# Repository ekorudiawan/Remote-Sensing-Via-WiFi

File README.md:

# Remote-Sensing-Via-WiFi
Remote Sensing Via WiFi

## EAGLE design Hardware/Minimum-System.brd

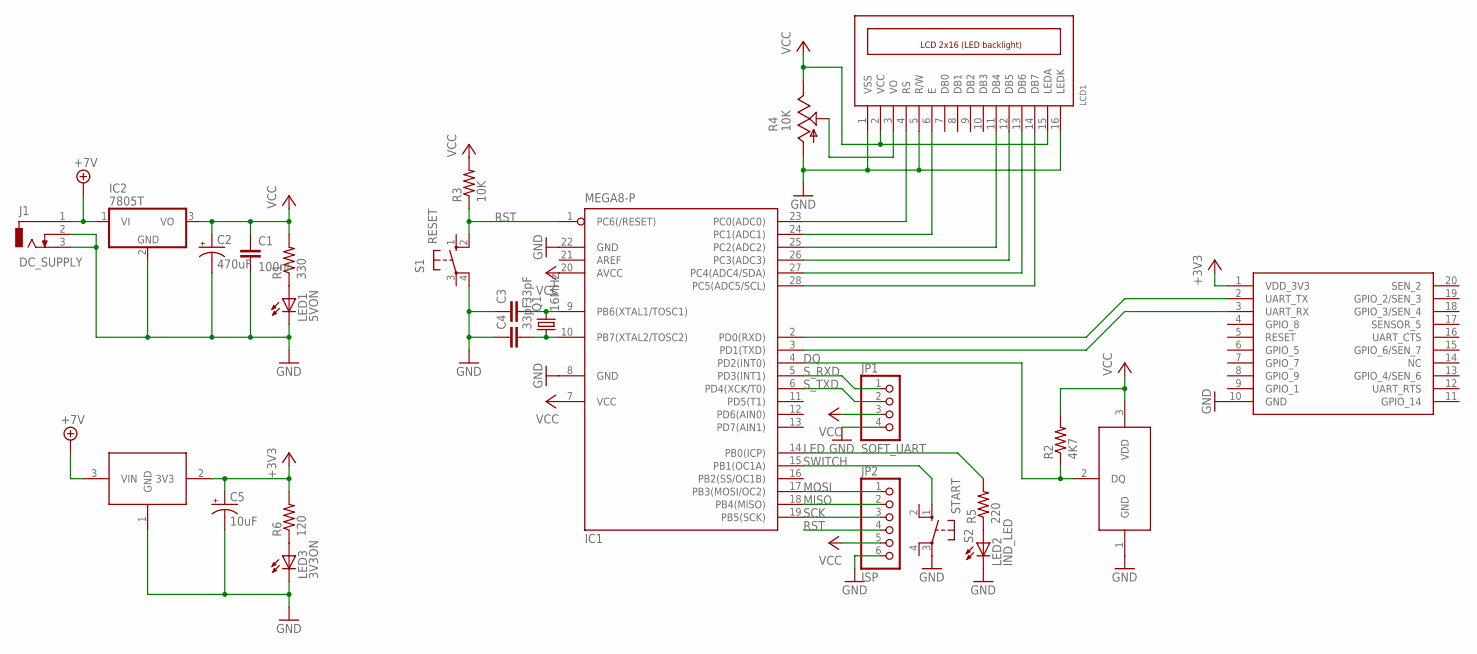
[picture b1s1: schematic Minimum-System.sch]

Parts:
C1: 100nF; C025-024X044
C2: 470uF; E2,5-7
C3, C4: 33pF; C025-024X044
C5: 10uF; E2,5-7
IC1: MEGA8-P; DIL28-3
IC2: 7805T; TO220H
J1: DC_SUPPLY; DCJ0202
JP1: SOFT_UART; 1X04
JP2: ISP; 1X06
LCD1: LCD_2X16; HY-1602F
LED1: 5VON; LED3MM
LED2: IND_LED; LED3MM
LED3: 3V3ON; LED3MM
Q1: 16MHz; HC49/S
R1: 330; 0207/10
R2: 4K7; 0207/10
R3: 10K; 0207/10
R4: 10K; CA6V
R5: 220; 0207/10
R6: 120; 0207/10
S1: RESET; B3F-10XX
S2: START; B3F-10XX
U1: DS1820; TO92
U2: LD1117V33; TO220
U3: WIFLY; WIFLY_SOCKET

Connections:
+3V3: C5.+, R6.2, U2.2 (3V3), U3.1 (VDD_3V3)
+7V: IC2.1 (VI), J1.1, U2.3 (VIN)
DQ: IC1.4 (PD2(INT0)), R2.1, U1.2 (DQ)
GND: C1.2, C2.-, C3.1, C4.1, C5.-, IC1.8 (GND), IC1.22 (GND), IC2.2 (GND), J1.2, J1.3, JP1.4, JP2.6, LCD1.1 (VSS), LCD1.5 (R/W), LCD1.16 (LEDK), LED1.K (C), LED2.K (C), LED3.K (C), R4.A, S1.4 (P1), S2.3, U1.1 (GND), U2.1 (GND), U3.10 (GND)
LED: IC1.14 (PB0(ICP)), R5.2
MISO: IC1.18 (PB4(MISO)), JP2.2
MOSI: IC1.17 (PB3(MOSI/OC2)), JP2.1
unnamed: LED1.A, R1.1
unnamed: IC1.25 (PC2(ADC2)), LCD1.11 (DB4)
unnamed: LCD1.3 (VO), R4.S
unnamed: IC1.23 (PC0(ADC0)), LCD1.4 (RS)
unnamed: C3.2, IC1.9 (PB6(XTAL1/TOSC1)), Q1.2
unnamed: C4.2, IC1.10 (PB7(XTAL2/TOSC2)), Q1.1
unnamed: IC1.24 (PC1(ADC1)), LCD1.6 (E)
unnamed: IC1.26 (PC3(ADC3)), LCD1.12 (DB5)
unnamed: IC1.27 (PC4(ADC4/SDA)), LCD1.13 (DB6)
unnamed: IC1.28 (PC5(ADC5/SCL)), LCD1.14 (DB7)
unnamed: IC1.2 (PD0(RXD)), U3.2 (UART_TX)
unnamed: IC1.3 (PD1(TXD)), U3.3 (UART_RX)
unnamed: LED2.A, R5.1
unnamed: LED3.A, R6.1
RST: IC1.1 (PC6(/RESET)), JP2.4, R3.1, S1.2 (S1)
SCK: IC1.19 (PB5(SCK)), JP2.3
SWITCH: IC1.15 (PB1(OC1A)), S2.1 (S)
S_RXD: IC1.5 (PD3(INT1)), JP1.1
S_TXD: IC1.6 (PD4(XCK/T0)), JP1.2
VCC: C1.1, C2.+, IC1.7 (VCC), IC1.20 (AVCC), IC2.3 (VO), JP1.3, JP2.5, LCD1.2 (VCC), LCD1.15 (LEDA), R1.2, R2.2, R3.2, R4.E, U1.3 (VDD)

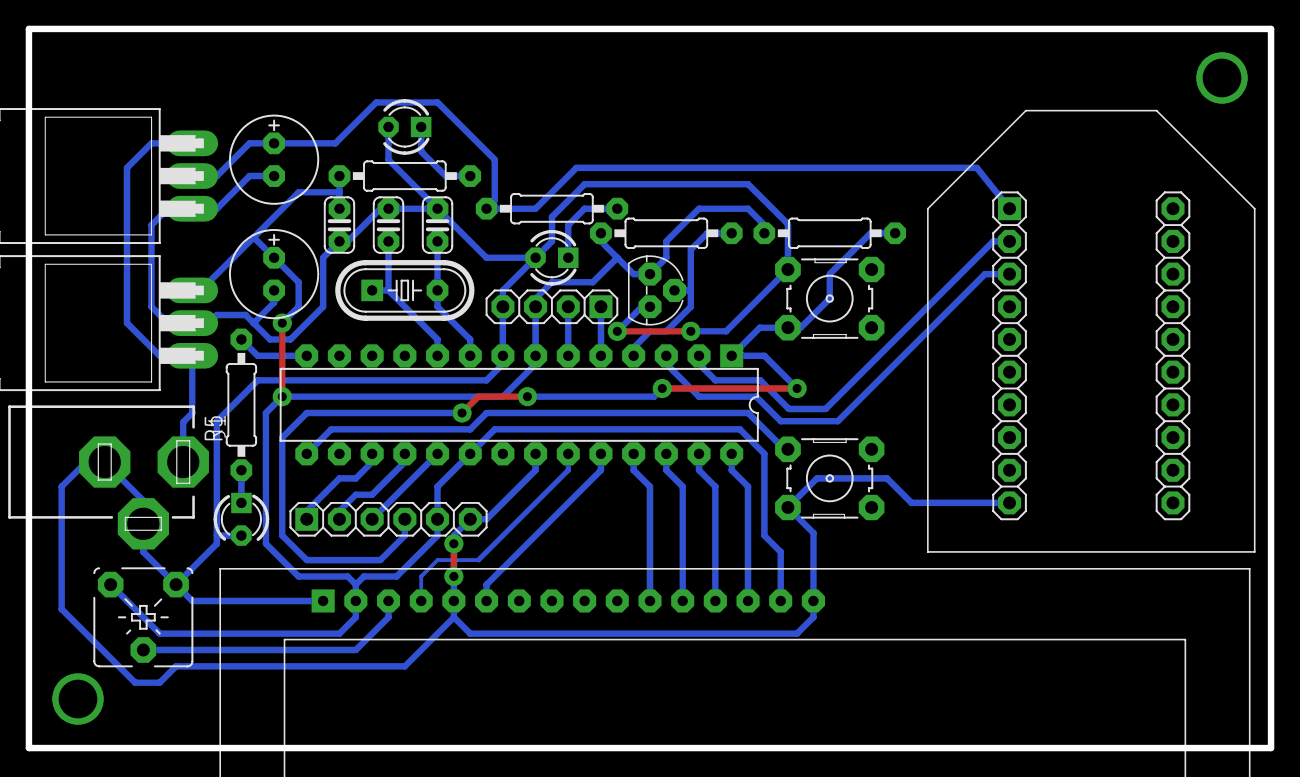
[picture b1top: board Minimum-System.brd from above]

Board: 2 copper layers, 96.5 x 55.9 mm, 26 parts (0 on the bottom side), 27 nets.

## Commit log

2017-10-03 Added HW & SW Source Files
